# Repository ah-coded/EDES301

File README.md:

<h1> EDES 301 </h1>
Repository for EDES301 course work

Project_01 Contains code to run the wificar, including the code for both the Laptop side and Pocketbeagle side.
NOTE! Ensure to input your own hotspot IP address before attempting to test. 

Project_02 Contains files to generate a ESP32 version of the project, with a custom footprint for the ESP32. 

Link to Hackster page: https://www.hackster.io/ah275/wrc-wifi-rally-car-f0a445

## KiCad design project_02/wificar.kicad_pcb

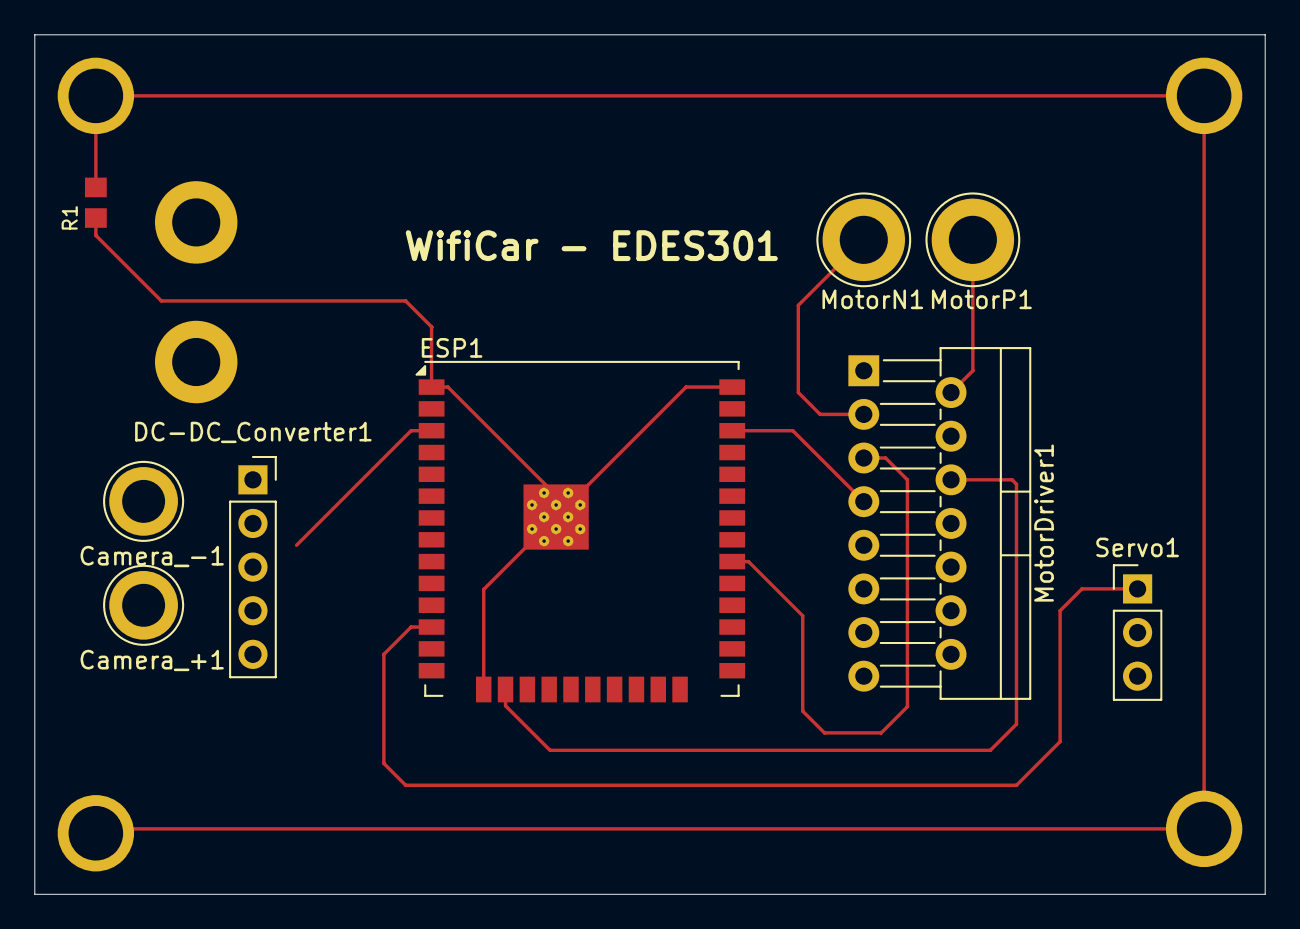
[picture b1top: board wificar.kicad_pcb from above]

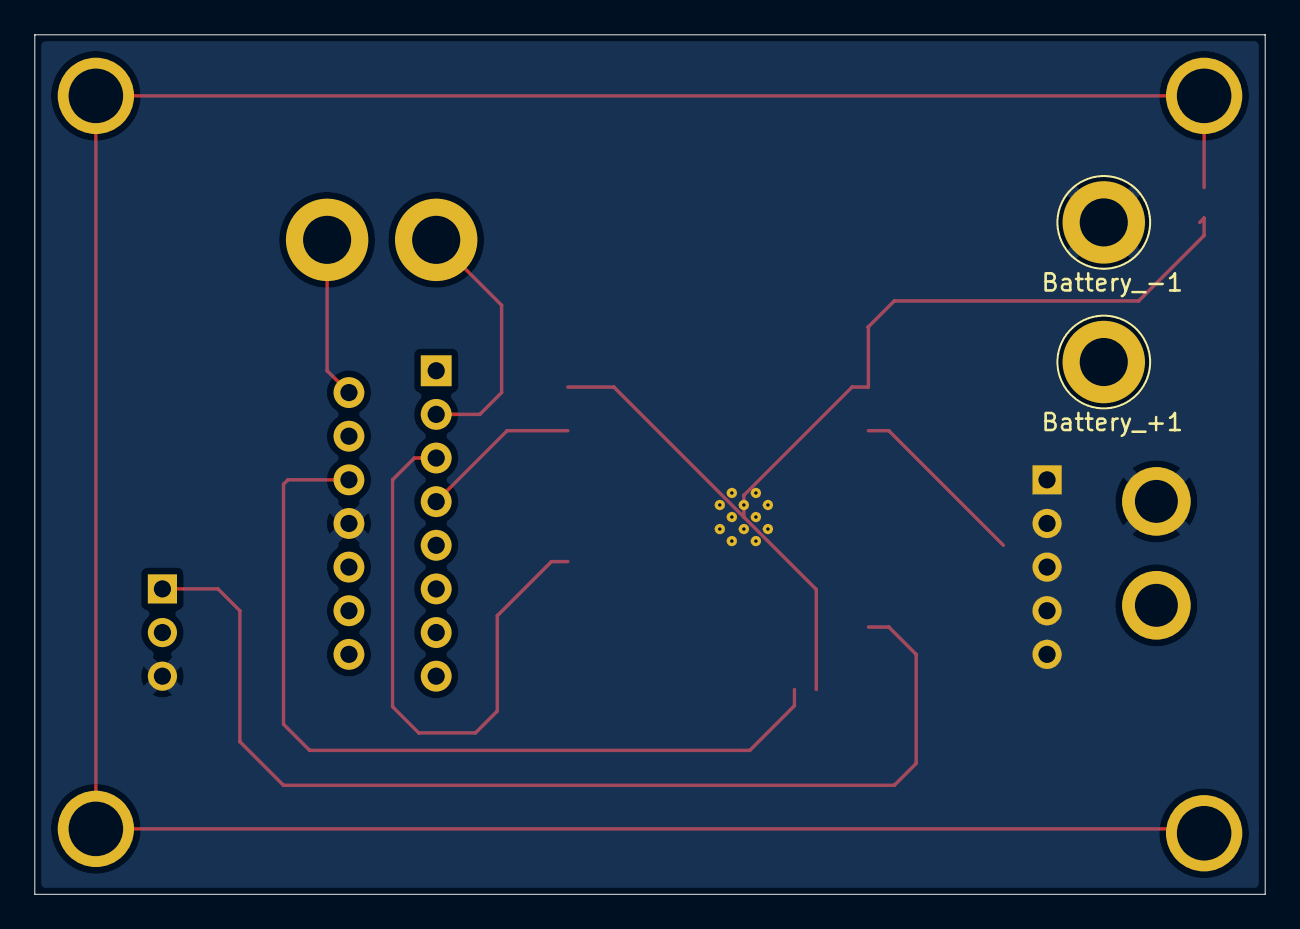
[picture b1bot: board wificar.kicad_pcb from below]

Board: 4 copper layers, 71.6 x 50.0 mm, 15 parts (2 on the bottom side), 10 nets.

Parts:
Battery_+1: TestPoint_Loop_D3.80mm_Drill2.8mm
Battery_-1: TestPoint_Loop_D3.80mm_Drill2.8mm
Camera_+1: TestPoint_Loop_D3.80mm_Drill2.5mm
Camera_-1: TestPoint_Loop_D3.80mm_Drill2.5mm
DC-DC_Converter1: LM2596S-5; PinSocket_1x05_P2.54mm_Vertical
ESP1: ESP32-WROOM-32U
M1, M2, M3, M4: MOUNTING_HOLE
MotorDriver1: L298N; TO-220-15_P2.54x5.08mm_StaggerOdd_Lead4.58mm_Vertical
MotorN1: TestPoint_Loop_D3.80mm_Drill2.8mm
MotorP1: TestPoint_Loop_D3.80mm_Drill2.8mm
R1: R0805
Servo1: Motor_Servo; PinHeader_1x03_P2.54mm_Vertical

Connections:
+5V: Camera_+1.1 (1_1), DC-DC_Converter1.2 (OUT), ESP1.3 (EN), Servo1.2 (+)
+12V: Battery_+1.1 (1_1), DC-DC_Converter1.1 (VIN), MotorDriver1.4 (Vs)
GND: Battery_-1.1 (1_1), Camera_-1.1 (1_1), DC-DC_Converter1.3 (GND), DC-DC_Converter1.5 (~ON/OFF), ESP1.1 (GND), ESP1.15 (GND), ESP1.38 (GND), ESP1.39 (GND), MotorDriver1.8 (GND), R1.1, Servo1.3 (-)
GNDPWR: M1.1 (1_1), M2.1 (1_1), M3.1 (1_1), M4.1 (1_1), R1.2
MotorIN1: ESP1.30 (IO18), MotorDriver1.5 (IN1)
MotorIN2: ESP1.36 (IO22), MotorDriver1.7 (IN2)
Motor_PWM: ESP1.16 (IO13), MotorDriver1.6 (EnA)
unnamed: MotorDriver1.2 (OUT1), MotorN1.1 (1_1)
unnamed: MotorDriver1.3 (OUT2), MotorP1.1 (1_1)
Servo_PWM: ESP1.12 (IO27), Servo1.1 (PWM)

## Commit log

2026-02-24 updating bugs
2026-02-24 assignment 4
2026-02-24 assignment 4 calc fix
2026-02-24 button works
2026-04-24 Rename python/access.py to python/wificar/access.py
2026-04-24 Rename python/configure_pins.sh to python/wificar/configure_pins.sh
2026-04-24 Rename python/run.sh to python/wificar/run.sh
2026-04-24 Rename python/wificar/access.py to python/wificar/pocketBeagle/access.py
2026-04-24 Rename python/wificar/configure_pins.sh to python/wificar/pocketBeagle/configure_pins.sh
2026-04-24 Rename python/wificar/run.sh to python/wificar/pocketBeagle/run.sh
2026-05-02 Create hardware
2026-05-02 Create python
2026-05-02 Rename python/wificar/laptopCode/CarWifi.py to project_01/python/wificar/laptopCode/CarWifi.py
2026-05-02 Rename python/wificar/laptopCode/VideoCapture.py to project_01/python/wificar/laptopCode/VideoCapture.py
2026-05-02 Rename python/wificar/pocketBeagle/access.py to project_01/python/wificar/pocketBeagle/access.py
2026-05-02 Rename python/wificar/pocketBeagle/configure_pins.sh to project_01/python/wificar/pocketBeagle/configure_pins.sh
2026-05-02 Rename python/wificar/pocketBeagle/run.sh to project_01/python/wificar/pocketBeagle/run.sh
2026-05-02 Rename project_02/placeholder.txt to project_02/MFG/placeholder.txt
2026-05-02 Rename placeholder.txt to placeholder.txt
